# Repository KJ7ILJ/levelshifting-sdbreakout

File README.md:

# levelshifting-sdbreakout
A level shifting SD breakout board compatible with 3.3V to 5V logic.

-CAMOutputs: Current Gerber and .XLN files for PCB production <br/>
-All .brd and .sch files are Eagle board and schematic files, respectively <br/>
-partslist.txt contains the part numbers and quantities for every component needed to build one of these breakout boards <br/>

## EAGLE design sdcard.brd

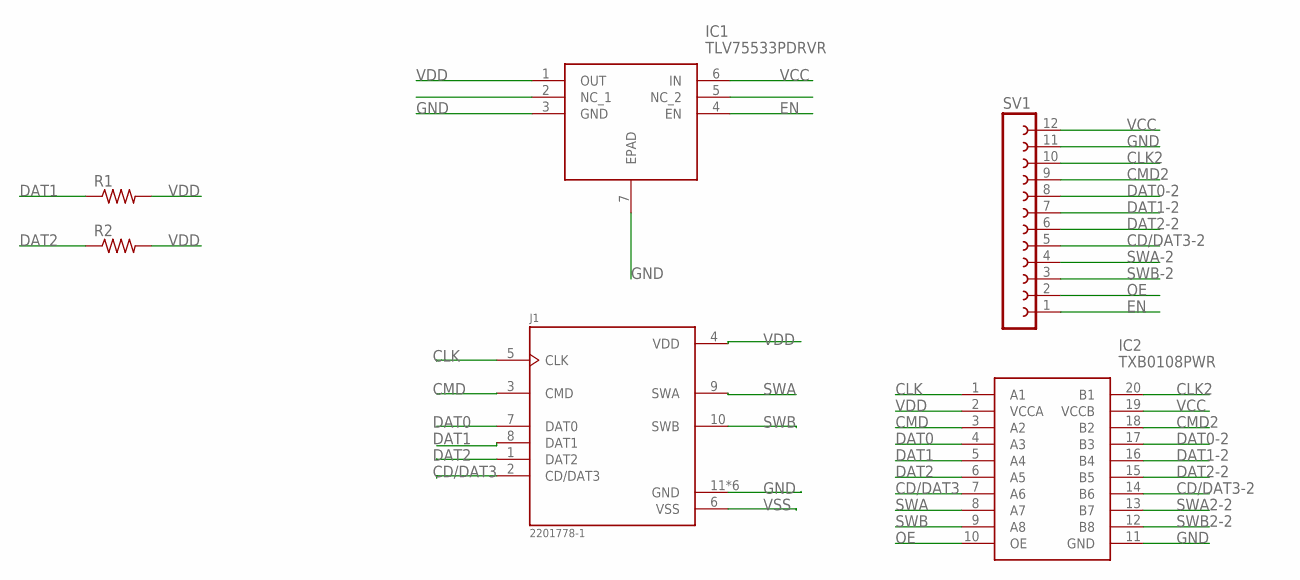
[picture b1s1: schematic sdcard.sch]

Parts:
IC1: TLV75533PDRVR; SON65P200X200X80-7N
IC2: TXB0108PWR; SOP65P640X120-20N
J1: 2201778-1; TE_2201778-1
R1, R2: R-US_R0603; R0603
SV1: FE12-1; FE12

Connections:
CD/DAT3: IC2.7 (A6), J1.2 (CD/DAT3)
CD/DAT3-2: IC2.14 (B6), SV1.5
CLK: IC2.1 (A1), J1.5 (CLK)
CLK2: IC2.20 (B1), SV1.10
CMD: IC2.3 (A2), J1.3 (CMD)
CMD2: IC2.18 (B2), SV1.9
DAT0: IC2.4 (A3), J1.7 (DAT0)
DAT0-2: IC2.17 (B3), SV1.8
DAT1: IC2.5 (A4), J1.8 (DAT1), R1.1
DAT1-2: IC2.16 (B4), SV1.7
DAT2: IC2.6 (A5), J1.1 (DAT2), R2.1
DAT2-2: IC2.15 (B5), SV1.6
EN: IC1.4 (EN), SV1.1
GND: IC1.3 (GND), IC1.7 (EPAD), IC2.11 (GND), J1.11 (GND), J1.12 (GND), J1.13 (GND), J1.14 (GND), J1.15 (GND), J1.16 (GND), SV1.11
OE: IC2.10 (OE), SV1.2
SWA: IC2.8 (A7), J1.9 (SWA)
SWA2-2: IC2.13 (B7)
SWA-2: SV1.4
SWB: IC2.9 (A8), J1.10 (SWB)
SWB2-2: IC2.12 (B8)
SWB-2: SV1.3
VCC: IC1.6 (IN), IC2.19 (VCCB), SV1.12
VDD: IC1.1 (OUT), IC2.2 (VCCA), J1.4 (VDD), R1.2, R2.2
VSS: J1.6 (VSS)

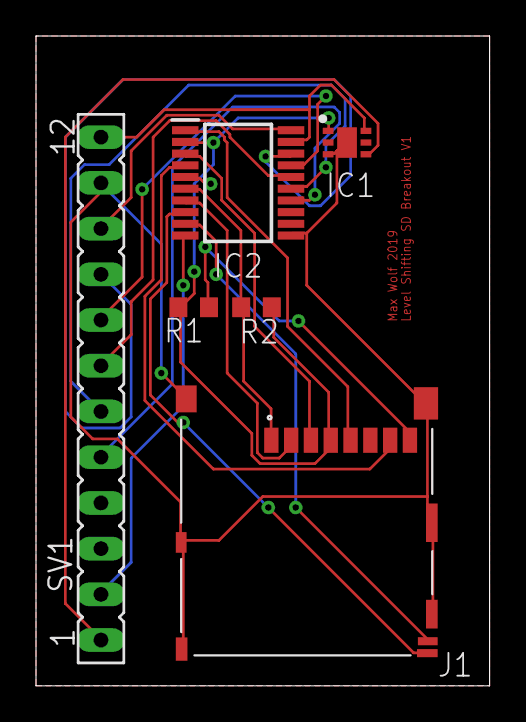
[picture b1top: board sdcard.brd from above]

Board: 2 copper layers, 25.2 x 36.1 mm, 6 parts (0 on the bottom side), 19 nets.

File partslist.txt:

LS-SD Breakout V1 Parts List:
	-QTY-PRT
	-1-TLV75533PDRVR
	-1-12PIN-FHEADER
	-1-TXB0108PWR
	-2-AC0603FR-104K75L
	-1-2201778-1

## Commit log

2019-07-21 Initial file commit.
